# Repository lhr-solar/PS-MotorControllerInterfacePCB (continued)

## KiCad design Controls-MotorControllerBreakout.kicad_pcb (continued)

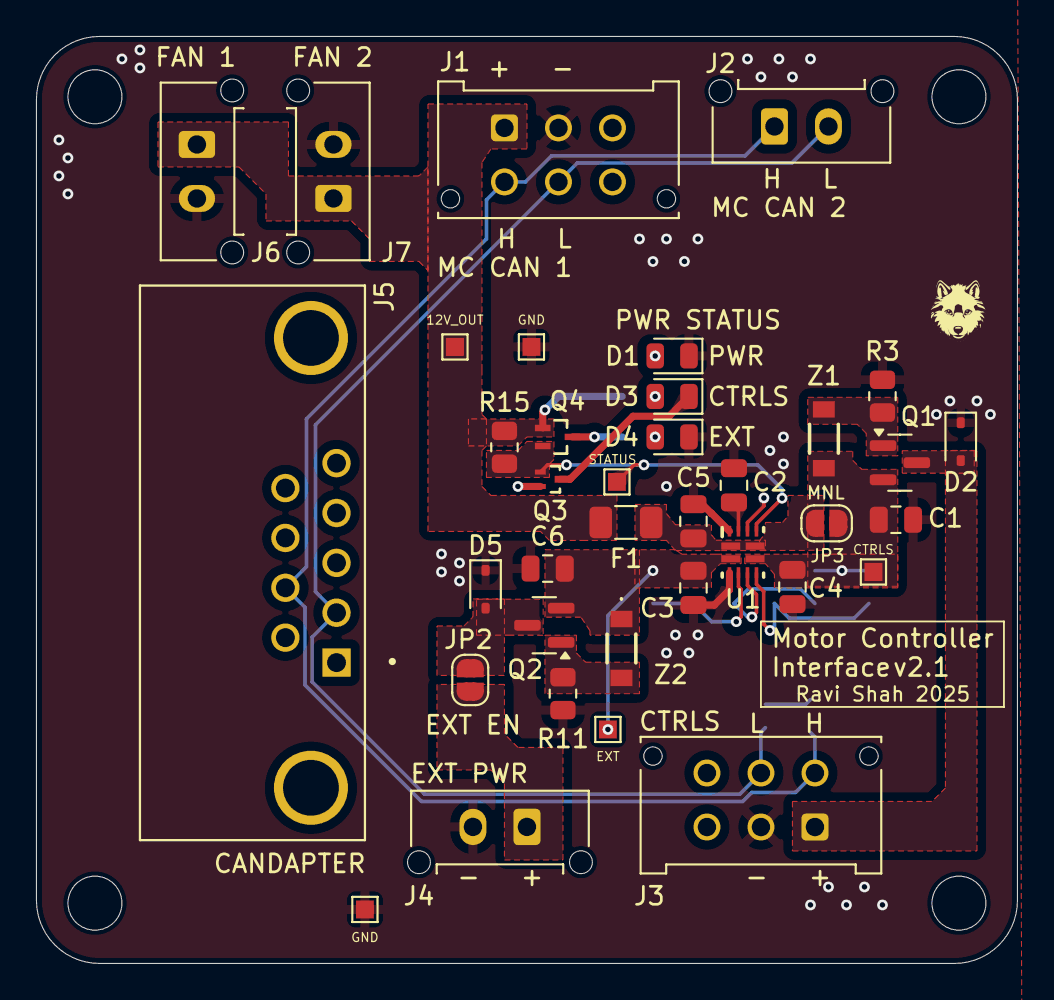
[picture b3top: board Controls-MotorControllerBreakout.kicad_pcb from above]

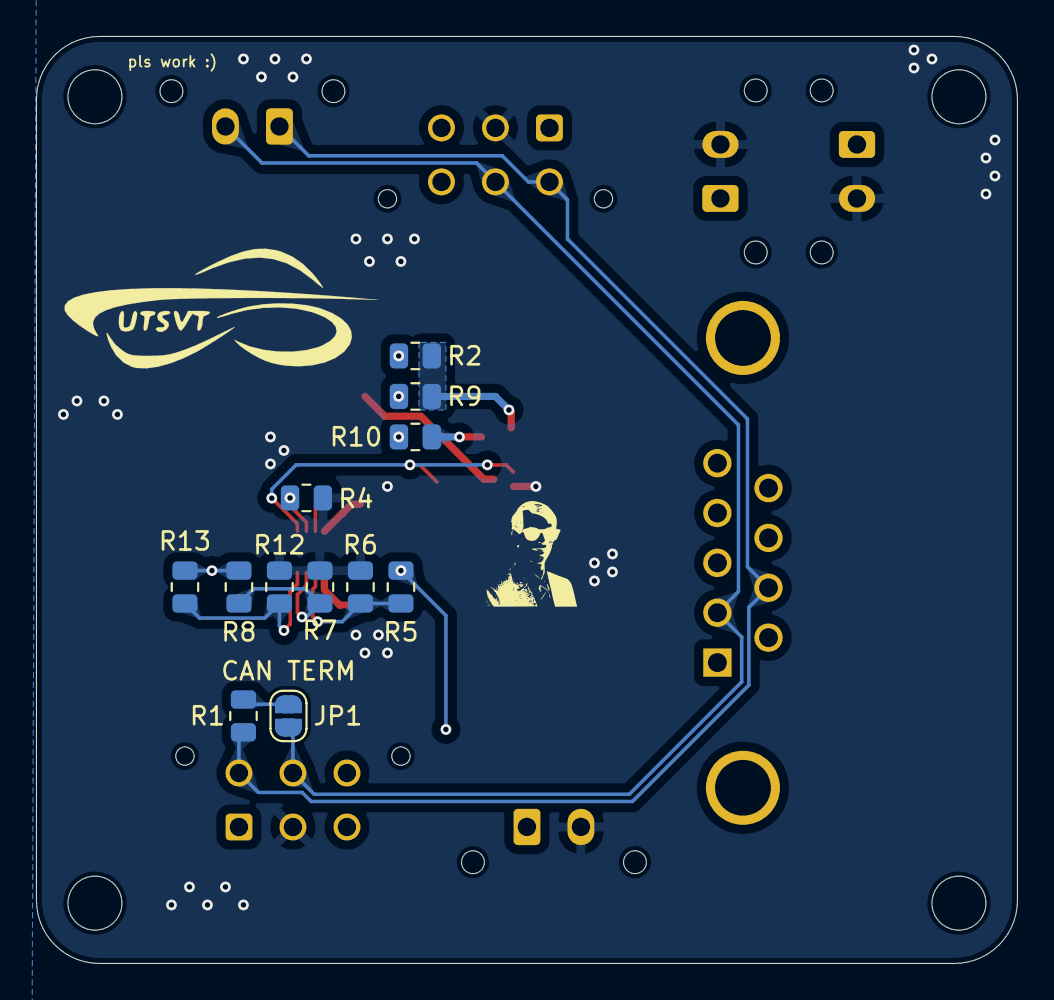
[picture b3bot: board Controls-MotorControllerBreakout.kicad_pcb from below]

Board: 2 copper layers, 54.5 x 51.5 mm, 54 parts (13 on the bottom side), 24 nets.

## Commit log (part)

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2025-05-26 modify for PEAK candapter
2025-09-22 cleanup
2025-09-22 init project
2025-10-02 schematic
2025-10-02 added testpoints too
2025-10-03 changes + ioc
2025-10-03 small fix
2025-10-10 layout
2025-10-11 added more
2025-10-11 new review this
2025-10-12 Hello
2025-10-14 jolyn
2025-10-14 done
2025-10-14 fuse mouser part number
2025-10-25 production
2025-10-25 updated bom
2025-11-04 Rev A (#5)
    * cleanup
    * init project
    * sch
    * schematic
    * added testpoints too
    * changes + ioc
2025-11-10 Firmware
2025-11-10 firmware?
2025-12-06 software pr
2025-12-15 mae flash
2025-12-21 revB
2025-12-28 re add kicad sharepoint
2025-12-28 schematic changes, pre pcb revB changes
2025-12-31 revB, will make aesthetic changes
2026-01-02 revB layout
2026-01-06 sch changes, pre pcb changes
2026-01-06 fuse fix
2026-01-09 layout ready for review
2026-01-10 layout done
2026-01-10 layout changes made
2026-01-10 done?
2026-01-10 ready
2026-01-11 done with changes
2026-01-11 small change
2026-01-11 minor layout aesthetic changes
2026-01-12 done changes
2026-01-13 finished LCSC
2026-01-13 minor fix
2026-01-13 fixed references and changed the labels
2026-01-13 standardized some lcsc
2026-01-15 removed firmware from revb i think?
2026-01-15 clean PR i hope
2026-01-15 RevB: reset KiCAD-Sharepoint submodule pointer
2026-01-15 firmware should be gonegit status
    ''
2026-01-15 clean up
2026-01-15 deletes
2026-01-15 deletes and move step file
2026-01-15 more delete
2026-01-15 anotgehr delete
2026-01-16 Rev b (#7)
    * Firmware
    * firmware?
    * software pr
    * mae flash
    * revB
    * firmware
2026-01-21 firmware lakshay
2026-02-02 new Firmware PR
2026-02-06 remove broken
2026-02-06 Remove stale KiCAD-Sharepoint submodule index entry
2026-02-06 re-add kicad sharepoint
2026-02-06 tests, makefile update, changes
2026-02-07 added LED test and made changes
2026-02-13 pwm_test and driver
2026-02-13 fixes
2026-02-14 HSS EN work load test passed
2026-02-22 addressed reviews
2026-02-24 added workflow (hope it works), rtos low level drivers and tests working
2026-02-24 update submodule
2026-02-28 Rev B Drivers (#9)
    * new Firmware PR
    * remove broken
    * Remove stale KiCAD-Sharepoint submodule index entry
    * re-add kicad sharepoint
    * tests, makefile update, changes
    * added LED test and made changes
2026-03-07 store to test LEDs again
2026-03-14 can_send worky finally
2026-03-14 build action
2026-03-19 Review pls
2026-03-19 fix?
2026-03-23 can reviews
2026-03-25 lakshay reviews addressed, will add comments soon, some make errors will fix soon
2026-03-25 fixed make errors
2026-03-25 fix build?
2026-03-26 testing
2026-03-26 help
2026-03-26 ts fried the fans 😢
2026-04-02 yaippe
2026-04-08 changes addressed and working on moco
